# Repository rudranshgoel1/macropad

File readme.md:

# macropad

### Why did I make it?
bcz i need more hardware projects in my portfolio and also because it seemed like a fun hardware project which was kinda beginner friendly.

### What was the hardest part about this ?
honestly speaking, CAD.

Features:

- 8 Remappable Key Matrix for anything!
- ESP32C3 SuperMini as the main brain
- Custom PCB Art (really cool)
- Custom case

### Schematic

### PCB 

### Case

### 3D view of all parts 

link to full 3d thing-
https://cad.onshape.com/documents/f3f4d199ef23d310b3ca664c/w/34908b541132c21f4c70cc87/e/ea0e0a44c36532055dd3e013?renderMode=0&uiState=6ac56a265213d46a6705e1a3

## BOM

[BOM](BOM.csv)
|Name                           |Purpose                         |Quantity|Total Cost (USD)|Link                                                                                 |Distributor    |
|-------------------------------|--------------------------------|--------|----------------|-------------------------------------------------------------------------------------|---------------|
|ESP32-S3 SuperMini             |Main MCU                        |1       |7.4             |https://www.amazon.in/gp/product/B0H8YMNKHL                                          |Amazon         |
|Switches for Transmitter       |Switches for controlling the car|8       |0               |SELF SOURCED                                                                         |SELF SOURCED   |
|Keycaps for the switches       |Keycaps of the switches         |8       |0               |SELF SOURCED                                                                         |SELF SOURCED   |
|0.91 inch display              |Display                         |1       |2.2             |https://robu.in/product/0-91-inch-128x32-i2c-iic-serial-blue-oled-lcd-display-module/|Robu           |
|Case 3D Printed                |Case for the entire macropad    |1       |0               |Printing Legion                                                                      |Printing Legion|
|PCB of Transmitter AND Receiver|Main PCBs                       |5       |13.82           |https://jlcpcb.com/                                                                  |JLPCB          |
|                               |                                |        |                |                                                                                     |               |
|                               |                                |        |23.42           |                                                                                     |               |

## Total Pricing

Final Price comes out to be 5,430 INR ($57.1) [ SHIPPING INCLUDED ]

The pricing might slightly vary due to flash sales, and dollar market trends.

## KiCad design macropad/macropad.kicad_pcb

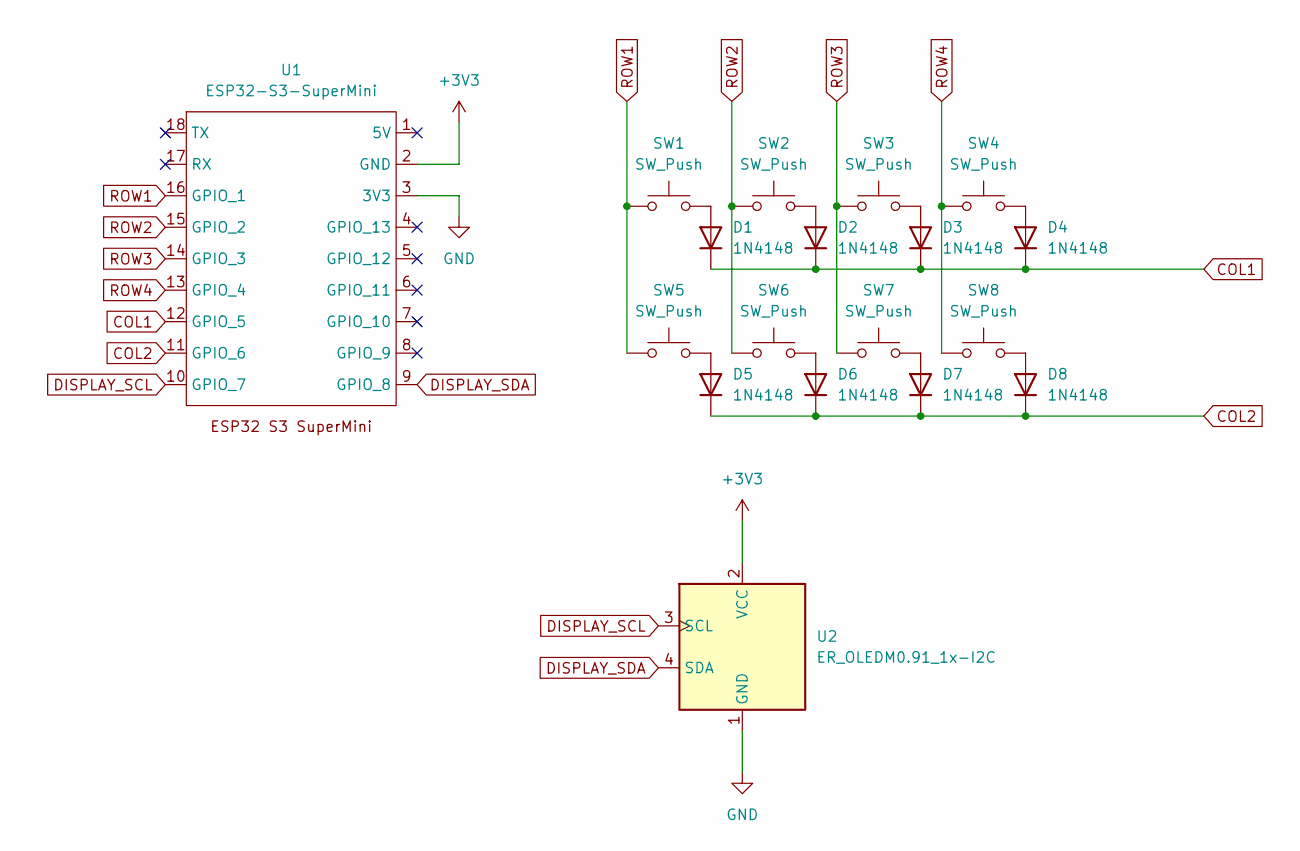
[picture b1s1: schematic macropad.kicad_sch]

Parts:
D1, D2, D3, D4, D5, D6, D7, D8: 1N4148; D_DO-35_SOD27_P7.62mm_Horizontal
SW1, SW2, SW3, SW4, SW5, SW6, SW7, SW8: SW_Push; SW_Cherry_MX_1.00u_PCB
U1: ESP32-S3-SuperMini
U2: ER_OLEDM0.91_1x-I2C

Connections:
+3V3: U1.2 (GND), U2.2 (VCC)
COL1: D1.1 (K), D2.1 (K), D3.1 (K), D4.1 (K), U1.12 (GPIO_5)
COL2: D5.1 (K), D6.1 (K), D7.1 (K), D8.1 (K), U1.11 (GPIO_6)
DISPLAY_SCL: U1.10 (GPIO_7), U2.3 (SCL)
DISPLAY_SDA: U1.9 (GPIO_8), U2.4 (SDA)
GND: U1.3 (3V3), U2.1 (GND)
unnamed: D1.2 (A), SW1.2
unnamed: D2.2 (A), SW2.2
unnamed: D3.2 (A), SW3.2
unnamed: D4.2 (A), SW4.2
unnamed: D5.2 (A), SW5.2
unnamed: D6.2 (A), SW6.2
unnamed: D7.2 (A), SW7.2
unnamed: D8.2 (A), SW8.2
ROW1: SW1.1, SW5.1, U1.16 (GPIO_1)
ROW2: SW2.1, SW6.1, U1.15 (GPIO_2)
ROW3: SW3.1, SW7.1, U1.14 (GPIO_3)
ROW4: SW4.1, SW8.1, U1.13 (GPIO_4)

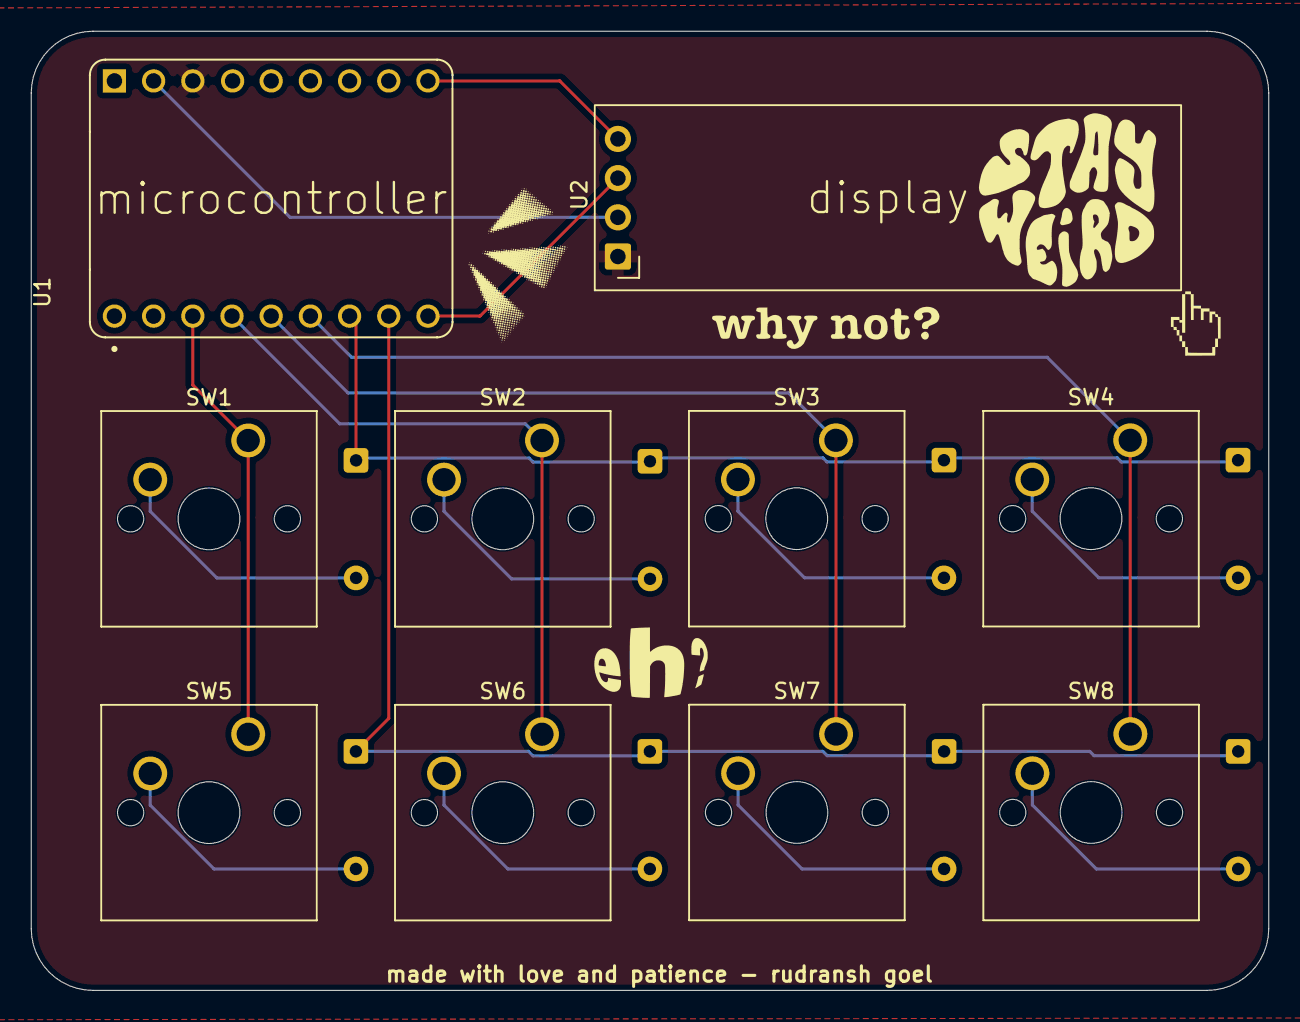
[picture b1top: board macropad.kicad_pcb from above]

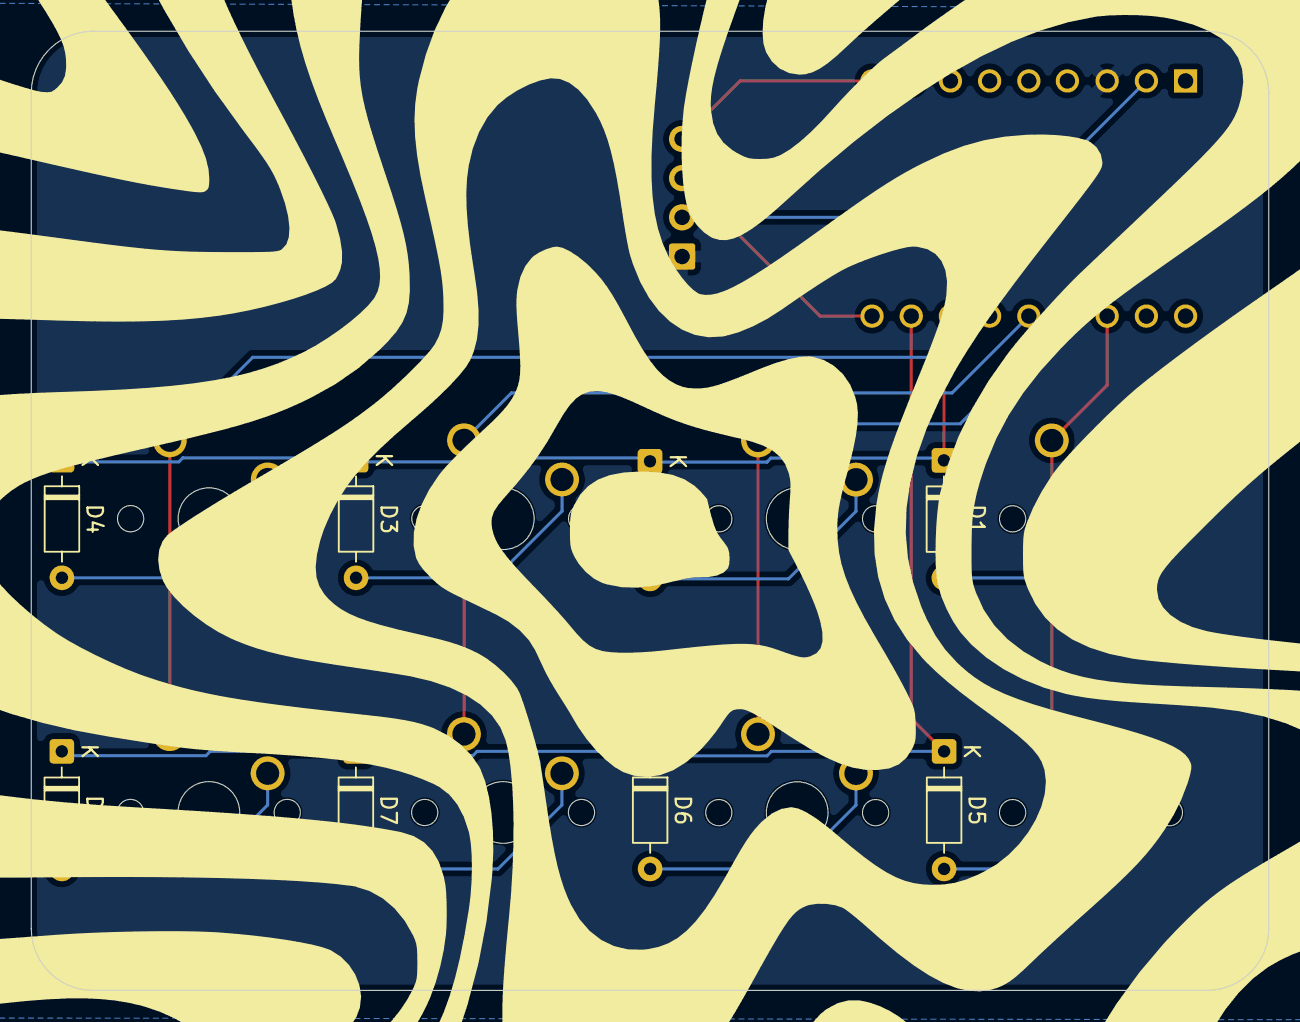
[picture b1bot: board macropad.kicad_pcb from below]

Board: 2 copper layers, 80.2 x 62.2 mm, 18 parts (8 on the bottom side), 18 nets.
